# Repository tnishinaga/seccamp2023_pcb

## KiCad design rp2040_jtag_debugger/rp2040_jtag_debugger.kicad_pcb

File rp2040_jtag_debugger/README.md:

# RP2040 JTAG Debugger

## Kicad Version

7.0.0

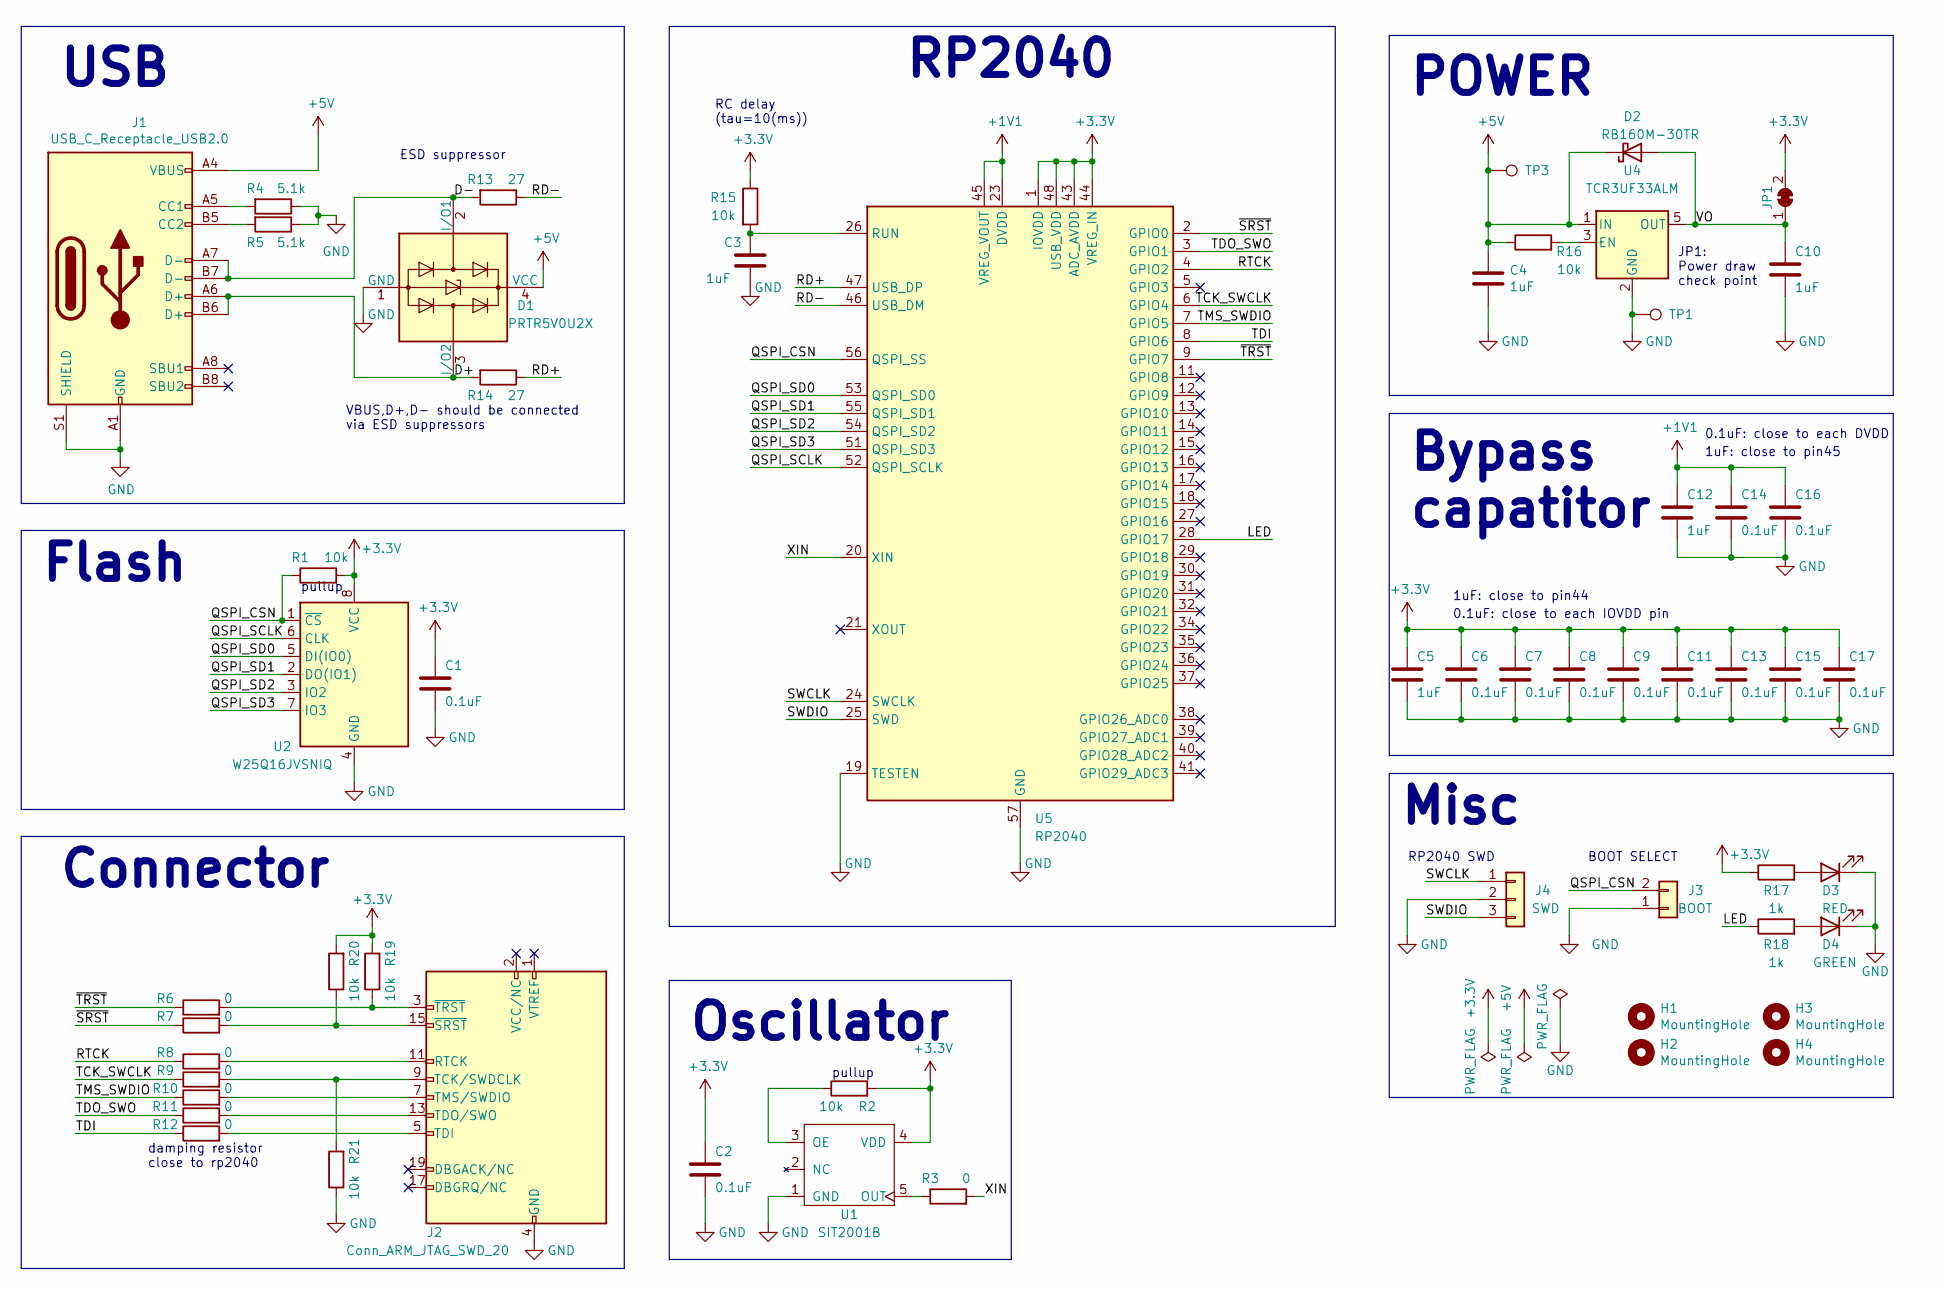
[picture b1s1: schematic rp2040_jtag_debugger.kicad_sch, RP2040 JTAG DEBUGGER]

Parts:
C1, C2, C6, C7, C8, C9, C11, C13, C14, C15, C16, C17: 0.1uF; C_0603_1608Metric; MPN C1608X7R1E104M080AA
C3: 1uF; C_0603_1608Metric; MPN C1608X7R1E104M080AA
C4, C10: 1uF; C_0603_1608Metric; MPN CL10A106MQ8NNNC
C5, C12: 1uF; C_0603_1608Metric; MPN C0603C105K8PACTU
D1: PRTR5V0U2X; SOT-143; MPN PRTR5V0U2X
D2: RB160M-30TR; D_PMDU; MPN RB160M-30TR
D3: RED; D_0603_1608Metric; MPN OSR50603C1E
D4: GREEN; D_0603_1608Metric; MPN OSG50603C1E
H1, H2, H3, H4: MountingHole; MountingHole_3mm
J1: USB_C_Receptacle_USB2.0; USB_C_Receptacle_HRO_TYPE-C-31-M-12; MPN 5077CR-16SMC2-BK-TR
J2: Conn_ARM_JTAG_SWD_20; IDC-Header_2x10_P2.54mm_Vertical
J3: BOOT; PinHeader_1x02_P1.27mm_Vertical
J4: SWD; PinHeader_1x03_P1.27mm_Vertical
JP1: Power draw check point; SolderJumper-2_P1.3mm_Bridged_Pad1.0x1.5mm
R1, R2, R15, R16, R19, R20, R21: 10k; R_0603_1608Metric; MPN ERJ-3EKF1002V
R3, R6, R7, R8, R9, R10, R11, R12: 0; R_0603_1608Metric; MPN RK73Z1JTTD
R4, R5: 5.1k; R_0603_1608Metric; MPN ERJ-3EKF5101V
R13, R14: 27; R_0603_1608Metric; MPN ERJ-3EKF27R0V
R17, R18: 1k; R_0603_1608Metric; MPN RC0603FR-131KL
TP1, TP3: TestPoint; TestPoint_Pad_D1.0mm
U1: SIT2001B; SOT-23-5; MPN SIT2001B
U2: W25Q16JVSNIQ; SOIC-8_5.23x5.23mm_P1.27mm; MPN W25Q16JVSNIQ
U4: TCR3UF33ALM; SOT-23-5; MPN TCR3UF33ALM
U5: RP2040; RP2040_QFN56_HandSolderHack; MPN RP2040

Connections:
+1V1: C12.1, C14.1, C16.1, U5.23 (DVDD), U5.45 (VREG_VOUT), U5.50 (DVDD)
+3.3V: C1.1, C2.1, C5.1, C6.1, C7.1, C8.1, C9.1, C11.1, C13.1, C15.1, C17.1, JP1.2 (B), R1.2, R2.2, R15.1, R17.1, R19.2, R20.2, U1.4 (VDD), U2.8 (VCC), U5.1 (IOVDD), U5.10 (IOVDD), U5.22 (IOVDD), U5.33 (IOVDD), U5.42 (IOVDD), U5.43 (ADC_AVDD), U5.44 (VREG_IN), U5.48 (USB_VDD), U5.49 (IOVDD)
+5V: C4.1, D1.4 (VCC), D2.1 (K), J1.A4 (VBUS), J1.A9 (VBUS), J1.B4 (VBUS), J1.B9 (VBUS), R16.1, TP3.1, U4.1 (IN)
/D+: D1.3 (I/O2), J1.A6 (D+), J1.B6 (D+), R14.2
/D-: D1.2 (I/O1), J1.A7 (D-), J1.B7 (D-), R13.2
/LED: R18.1, U5.28 (GPIO17)
/QSPI_CSN: J3.2, R1.1, U2.1 (~CS), U5.56 (QSPI_SS)
/QSPI_SCLK: U2.6 (CLK), U5.52 (QSPI_SCLK)
/QSPI_SD0: U2.5 (DI(IO0)), U5.53 (QSPI_SD0)
/QSPI_SD1: U2.2 (DO(IO1)), U5.55 (QSPI_SD1)
/QSPI_SD2: U2.3 (IO2), U5.54 (QSPI_SD2)
/QSPI_SD3: U2.7 (IO3), U5.51 (QSPI_SD3)
/RD+: R14.1, U5.47 (USB_DP)
/RD-: R13.1, U5.46 (USB_DM)
/RTCK: R8.1, U5.4 (GPIO2)
/SWCLK: J4.1, U5.24 (SWCLK)
/SWDIO: J4.3, U5.25 (SWD)
/TCK_SWCLK: R9.1, U5.6 (GPIO4)
/TDI: R12.1, U5.8 (GPIO6)
/TDO_SWO: R11.1, U5.3 (GPIO1)
/TMS_SWDIO: R10.1, U5.7 (GPIO5)
/VO: C10.1, D2.2 (A), JP1.1 (A), U4.5 (OUT)
/XIN: R3.2, U5.20 (XIN)
/~SRST: R7.1, U5.2 (GPIO0)
/~TRST: R6.1, U5.9 (GPIO7)
GND: C1.2, C2.2, C3.2, C4.2, C5.2, C6.2, C7.2, C8.2, C9.2, C10.2, C11.2, C12.2, C13.2, C14.2, C15.2, C16.2, C17.2, D1.1 (GND), D3.1 (K), D4.1 (K), J1.A1 (GND), J1.A12 (GND), J1.B1 (GND), J1.B12 (GND), J1.S1 (SHIELD), J2.4 (GND), J2.6 (GND), J2.8 (GND), J2.10 (GND), J2.12 (GND), J2.14 (GND), J2.16 (GND), J2.18 (GND), J2.20 (GND), J3.1, J4.2, R4.1, R5.1, R21.1, TP1.1, U1.1 (GND), U2.4 (GND), U4.2 (GND), U5.19 (TESTEN), U5.57 (GND)
unnamed: D3.2 (A), R17.2
unnamed: D4.2 (A), R18.2
unnamed: J1.A5 (CC1), R4.2
unnamed: J1.B5 (CC2), R5.2
unnamed: J2.11 (RTCK), R8.2
unnamed: J2.9 (TCK/SWDCLK), R9.2, R21.2
unnamed: J2.5 (TDI), R12.2
unnamed: J2.13 (TDO/SWO), R11.2
unnamed: J2.7 (TMS/SWDIO), R10.2
unnamed: J2.15 (~SRST), R7.2, R20.1
unnamed: J2.3 (~TRST), R6.2, R19.1
unnamed: R2.1, U1.3 (OE)
unnamed: R3.1, U1.5 (OUT)
unnamed: R16.2, U4.3 (EN)
unnamed: C3.1, R15.2, U5.26 (RUN)

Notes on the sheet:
Misc
Flash
RP2040
pullup
1uF: close to pin45
0.1uF: close to each IOVDD pin
POWER
VBUS,D+,D- should be connected via ESD suppressors
BOOT SELECT
damping resistor close to rp2040
RC delay (tau=10(ms))
Connector
RP2040 SWD
Oscillator
1uF: close to pin44
Bypass capatitor
0.1uF: close to each DVDD
JP1: Power draw check point
ESD suppressor
USB

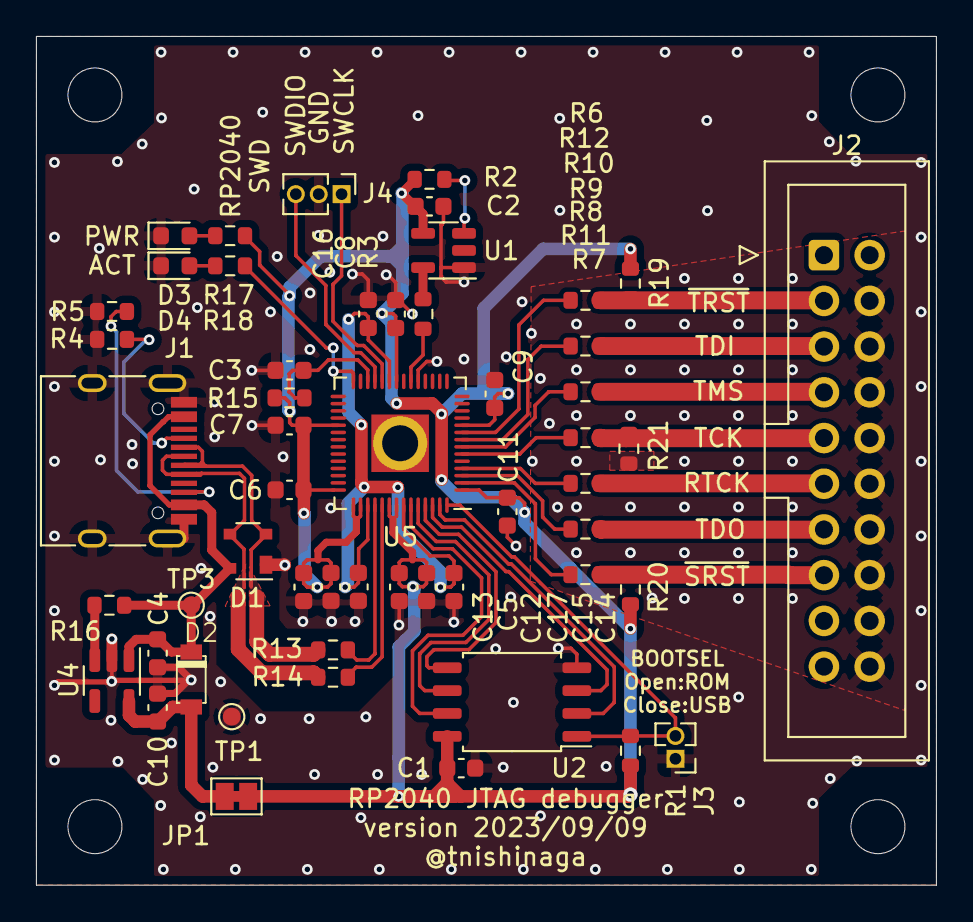
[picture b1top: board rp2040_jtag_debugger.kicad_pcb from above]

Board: 2 copper layers, 50.0 x 47.2 mm, 57 parts (0 on the bottom side), 41 nets.

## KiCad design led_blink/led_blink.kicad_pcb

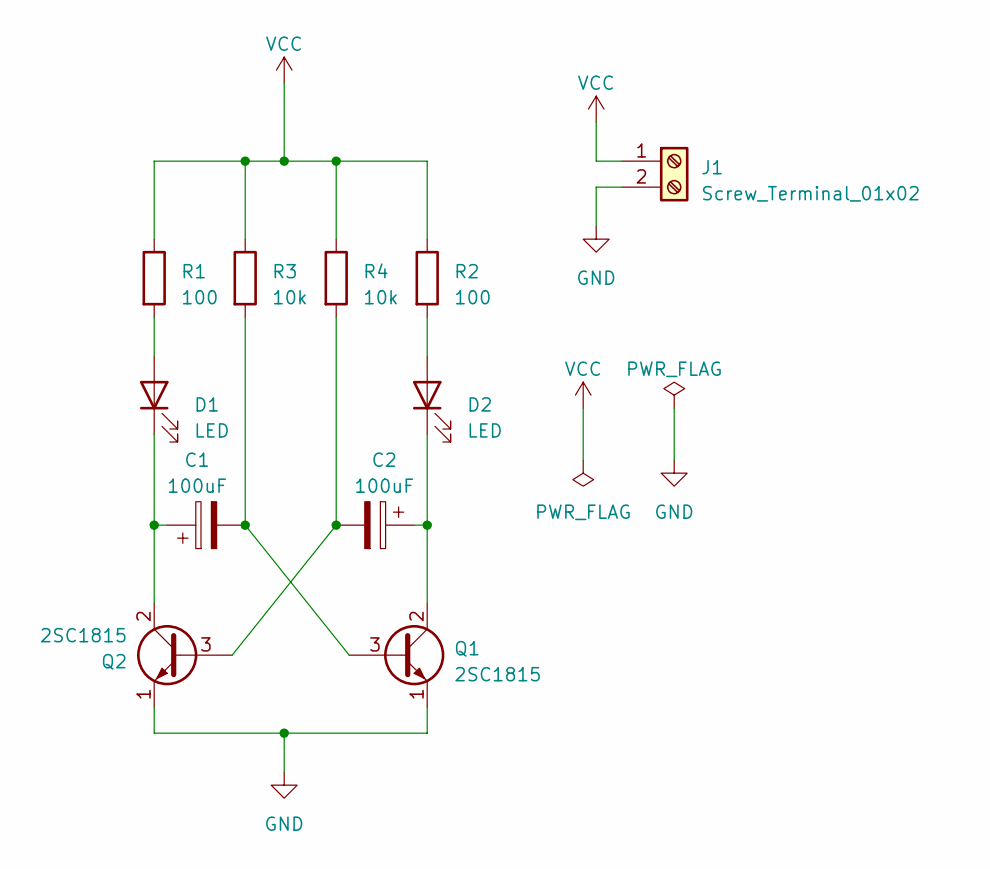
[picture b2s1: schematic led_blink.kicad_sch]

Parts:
C1, C2: 100uF; CP_Radial_D6.3mm_P2.50mm
D1, D2: LED; LED_D3.0mm
J1: Screw_Terminal_01x02; TerminalBlock_bornier-2_P5.08mm
Q1, Q2: 2SC1815; TO-92_Inline
R1, R2: 100; R_Axial_DIN0207_L6.3mm_D2.5mm_P10.16mm_Horizontal
R3, R4: 10k; R_Axial_DIN0207_L6.3mm_D2.5mm_P10.16mm_Horizontal

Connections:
GND: J1.2, Q1.1 (E), Q2.1 (E)
unnamed: D1.2 (A), R1.2
unnamed: C1.1, D1.1 (K), Q2.2 (C)
unnamed: D2.2 (A), R2.2
unnamed: C2.1, D2.1 (K), Q1.2 (C)
unnamed: C1.2, Q1.3 (B), R3.2
unnamed: C2.2, Q2.3 (B), R4.2
VCC: J1.1, R1.1, R2.1, R3.1, R4.1

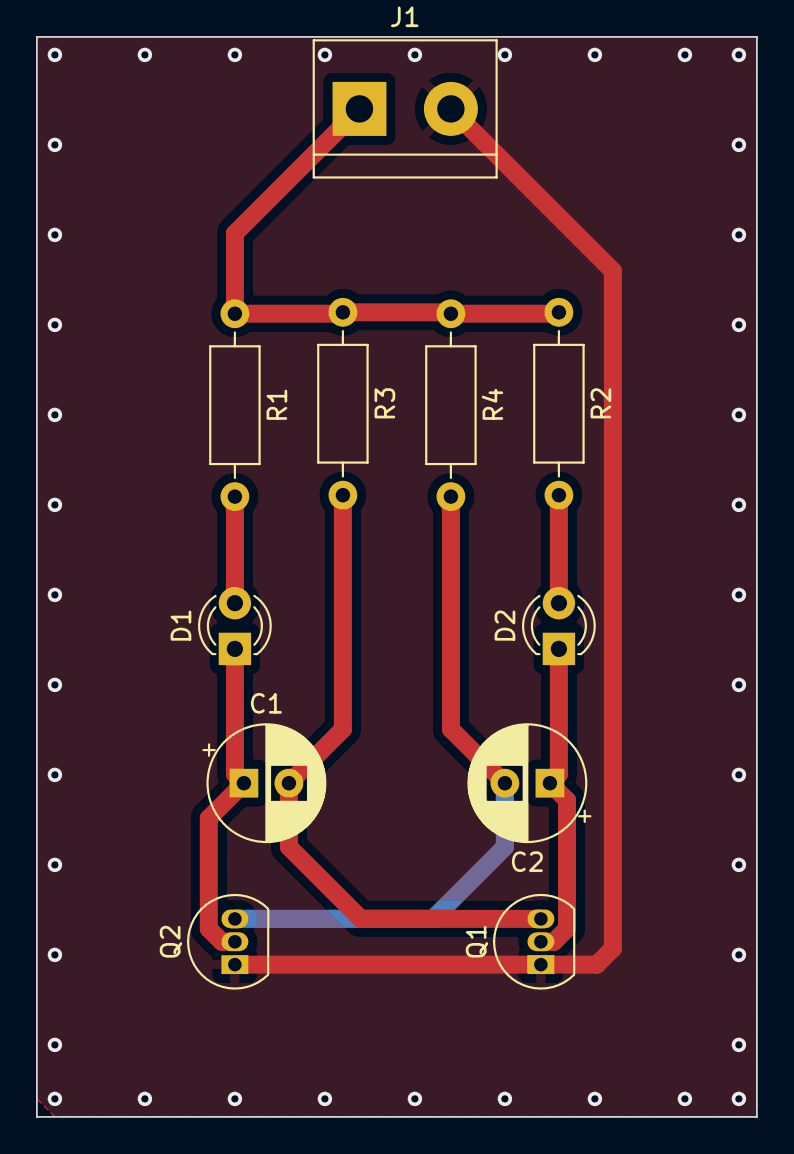
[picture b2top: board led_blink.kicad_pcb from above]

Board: 2 copper layers, 40.0 x 60.0 mm, 11 parts (0 on the bottom side), 8 nets.

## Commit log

2023-03-21 wip: fix DRC
2023-07-27 v2023.07.27
2023-09-09 update to 2023/09/09 version
